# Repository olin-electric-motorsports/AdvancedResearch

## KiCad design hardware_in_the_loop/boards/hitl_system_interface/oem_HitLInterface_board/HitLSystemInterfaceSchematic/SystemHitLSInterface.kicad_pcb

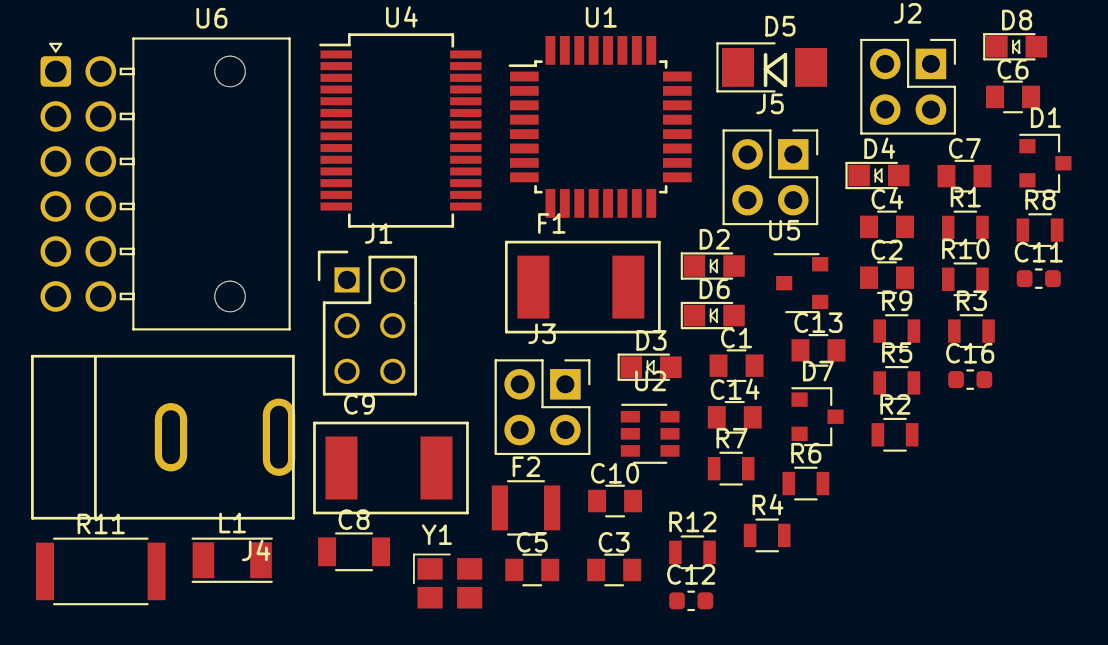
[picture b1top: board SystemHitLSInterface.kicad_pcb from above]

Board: 2 copper layers, 49 parts (0 on the bottom side), 44 nets, no tracks yet.

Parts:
C1, C3, C7, C13, C14: C_0.1uF; C_0805_OEM
C2: C_100pF; C_0805_OEM
C4, C6: C_30pF; C_0805_OEM
C5: C_2.2uF; C_0805_OEM
C8: C_22uF; C_1206_OEM
C9: C_33uF; Fuse_1812
C10: C_47uF; C_0805_OEM
C11: C_4.7uF; C_0603_1608Metric
C12, C16: C_100nF; C_0603_1608Metric
D1, D7: BAS40-00; SOT-23
D2, D3, D4, D6, D8: LED_0805; LED_0805_OEM
D5: D_Zener_18V; DO-214AA
F1: 200mA_Fuse; Fuse_1812
F2: F_500mA_16V; Fuse_1210
J1: CONN_02X03; Pin_Header_Straight_2x03
J2, J3, J5: Conn_01x04_Female; PinSocket_2x02_P2.54mm_Vertical
J4: Barrel_Jack; barrel_jack_PJ-037A
L1: L_100uH; L_100uH_OEM
R1: R_100; R_0805_OEM
R2, R3, R4, R12: R_200; R_0805_OEM
R5, R6, R7: R_10K; R_0805_OEM
R8: R_1K; R_0805_OEM
R9: R_25K; R_0805_OEM
R10: R_100K; R_0805_OEM
R11: R_0_2512; R_2512_OEM
U1: ATmega328P-AU; TQFP-32_7x7mm_P0.8mm
U2: TPS560430YF; SOT-23-6_OEM
U4: FT232RL; SSOP-28_5.3x10.2mm_P0.65mm
U5: LM3480; SOT-23-3_OEM
U6: NanoFit_RA_TH_12; NanoFit_RA_12
Y1: Crystal_SMD; Crystal_SMD_FA238

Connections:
+3V3: C14.1, J2.1, U5.1
/12V: C3.1, C5.1, D5.1, J2.3, R8.1, U2.4, U2.5
/AI1: U1.19, U6.8
/AI2: U1.22, U6.9
/AI3: U1.23, U6.10
/AI4: U1.24, U6.11
/D1: U1.25, U6.1
/D2: U1.26, U6.2
/D3: U1.32, U6.3
/D4: U1.1, U6.4
/D5: U1.11, U6.5
/D6: U1.12, U6.6
/D7: U1.13, U6.7
/MISO: J1.1, J3.4, U1.16
/MOSI: J1.4, J3.3, U1.15
/RESET: J1.5, R7.2, U1.29
/RXD: U1.30, U4.1
/SCK: J1.3, J3.2, U1.17
/SCL: J5.3, R6.2, U1.28
/SDA: J5.4, R5.2, U1.27
/SS_HitL: J3.1, U1.14
/TXD: U1.31, U4.5
/VCCUSB: C11.2, C12.2, D1.3, U4.20
GND: C1.2, C2.2, C3.2, C4.2, C5.2, C6.2, C8.2, C9.2, C10.2, C11.1, C12.1, C13.2, C14.2, C16.2, D2.1, D3.1, D4.1, D6.1, D8.1, F2.2, J1.6, J2.4, J4.1, R9.2, U1.3, U1.5, U1.21, U2.2, U4.7, U4.18, U4.21, U4.25, U4.26, U5.3, Y1.2, Y1.4
unnamed: C2.1, R1.2, U1.18
unnamed: C4.1, U1.8, Y1.1
unnamed: C6.1, U1.7, Y1.3
unnamed: C7.1, U2.1
unnamed: C7.2, L1.1, U2.6
unnamed: C8.1, C9.1, C10.1, L1.2, R10.1, R11.1
unnamed: C16.1, U4.17
unnamed: D1.1, F1.2
unnamed: D2.2, R2.1
unnamed: D3.2, R3.1
unnamed: D4.2, R4.1
unnamed: D5.2, F2.1
unnamed: D6.2, R8.2
unnamed: D7.1, R11.2, R12.1
unnamed: D8.2, R12.2
unnamed: R2.2, U1.2
unnamed: R3.2, U1.9
unnamed: R4.2, U1.10
unnamed: R9.1, R10.2, U2.3
VCC: C1.1, C13.1, D7.3, J1.2, J2.2, J4.2, R1.1, R5.1, R6.1, R7.1, U1.4, U1.6, U4.4, U5.2

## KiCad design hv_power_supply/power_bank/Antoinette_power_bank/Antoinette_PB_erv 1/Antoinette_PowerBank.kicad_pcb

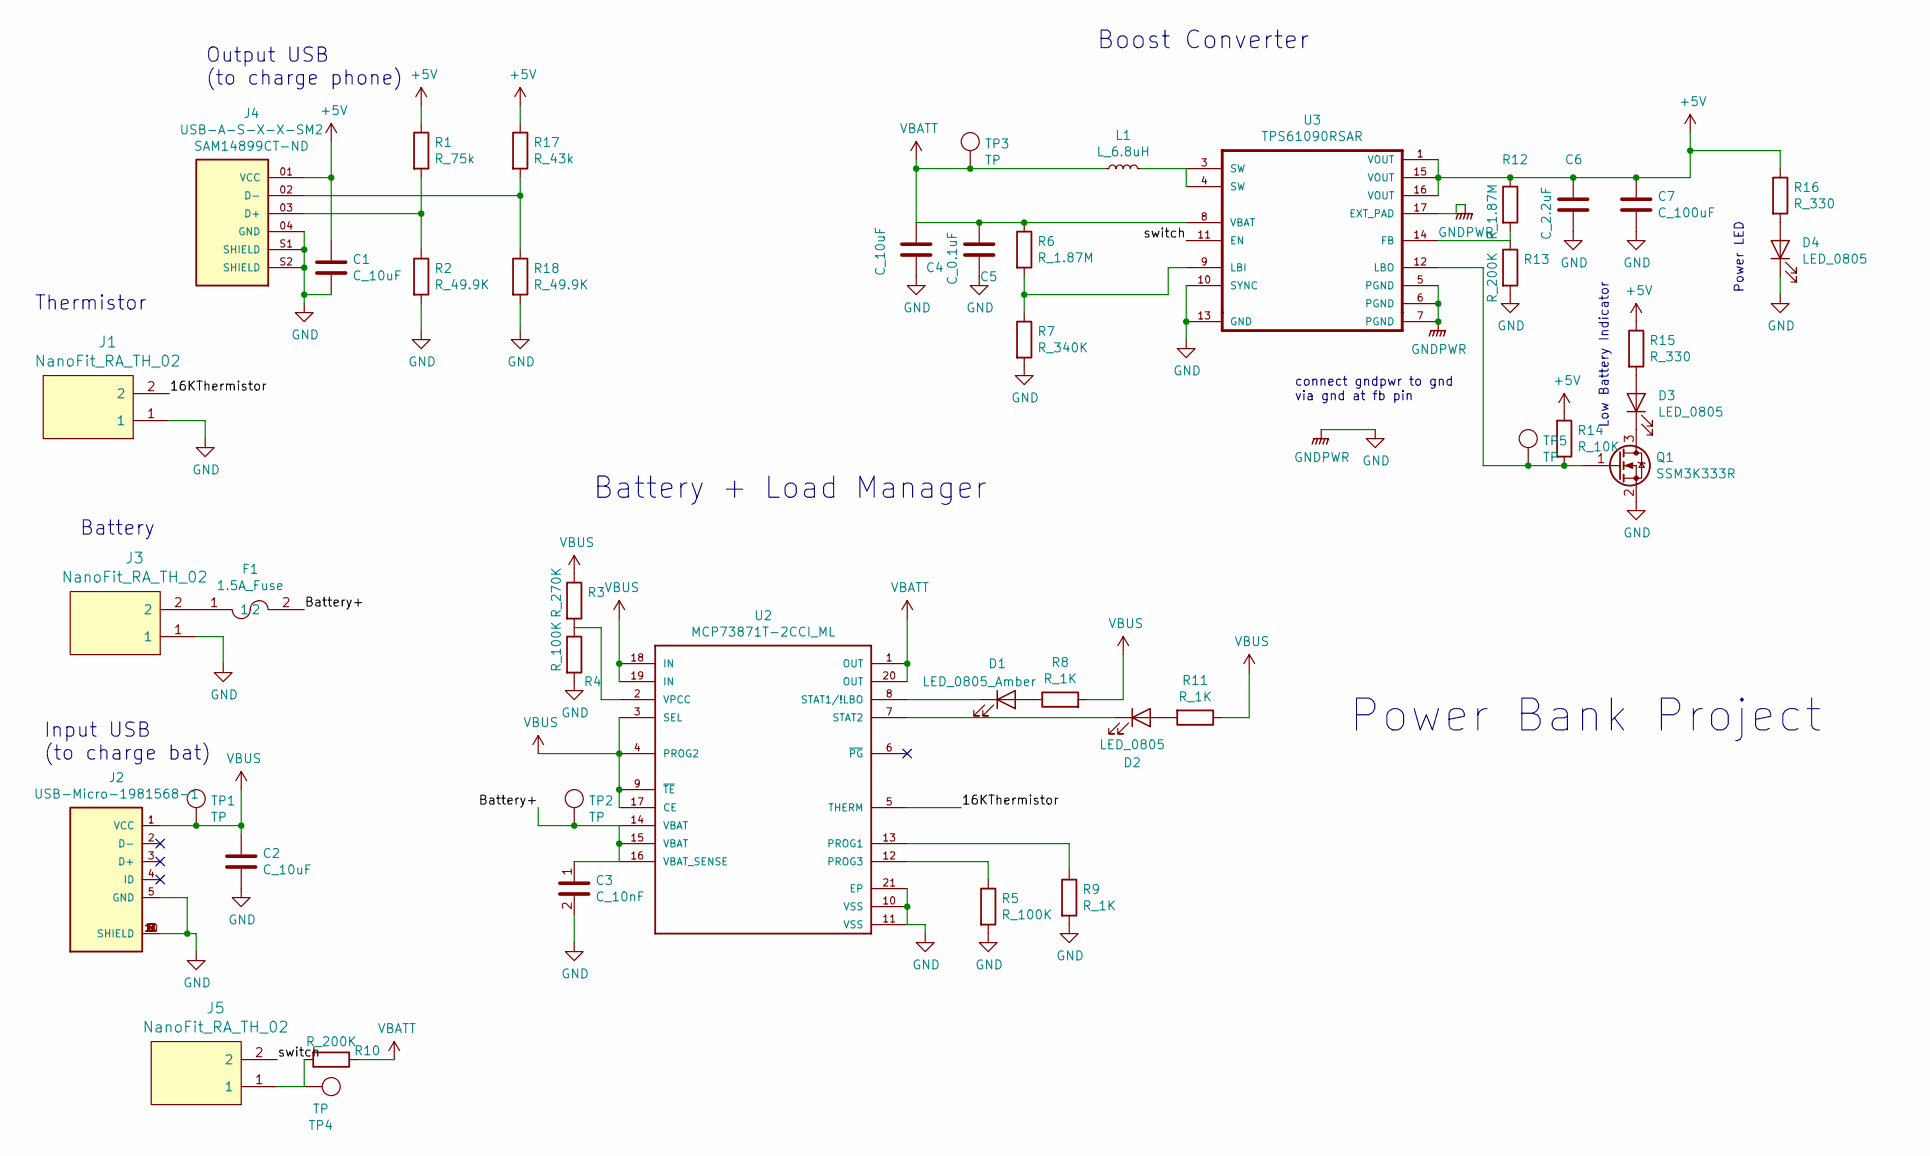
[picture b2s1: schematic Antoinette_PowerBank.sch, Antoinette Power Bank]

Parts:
C1, C2, C4: C_10uF; C_0805_OEM; MPN 1276-1052-1-ND
C3: C_10nF; C_0805_OEM; MPN 1276-1015-1-ND
C5: C_0.1uF; C_0805_OEM; MPN 478-3352-1-ND
C6: C_2.2uF; C_0805_OEM
C7: C_100uF; C_1812_4532Metric; MPN 445-1413-1-ND
D1: LED_0805_Amber; LED_0805_OEM; MPN L71517CT-ND
D2, D3, D4: LED_0805; LED_0805_OEM; MPN 475-1410-1-ND
F1: 1.5A_Fuse; Fuse_1206; MPN F1462CT-ND
J1, J3, J5: NanoFit_RA_TH_02; NanoFit_Molex_1x02x2.50mm_Angled_OEM; MPN WM14972-ND
J2: USB-Micro-1981568-1; TE_1981568-1; MPN 1981568-1
J4: USB-A-S-X-X-SM2; SAMTEC_USB-A-S-X-X-SM2; MPN SAM14899CT-ND
L1: L_6.8uH; L_100uH_OEM; MPN 445-1539-1-ND
Q1: SSM3K333R; SOT-23F; MPN SSM3K333RLFCT-ND
R1: R_75k; R_0805_OEM
R2, R18: R_49.9K; R_0805_OEM
R3: R_270K; R_0805_OEM; MPN P270KDACT-ND
R4, R5: R_100K; R_0805_OEM; MPN P100KCCT-ND
R6, R12: R_1.87M; R_0805_OEM; MPN RMCF0805FT1M82CT-ND
R7: R_340K; R_0805_OEM; MPN P300KDACT-ND
R8, R9, R11: R_1K; R_0805_OEM; MPN RNCP0805FTD1K00CT-ND
R10, R13: R_200K; R_0805_OEM; MPN P300KDACT-ND
R14: R_10K; R_0805_OEM; MPN CRS0805-FX-1002ELFCT-ND
R15, R16: R_330; R_0805_OEM; MPN RMCF0805FT330RCT-ND
R17: R_43k; R_0805_OEM
TP1, TP2, TP3, TP4, TP5: TP; tp_1.6mm; MPN 36-5006-ND
U2: MCP73871T-2CCI_ML; MCP73871T
U3: TPS61090RSAR

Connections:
+5V: C1.1, C6.1, C7.1, J4.01 (VCC), R1.1, R12.1, R14.1, R15.1, R16.1, R17.1, U3.1 (VOUT), U3.15 (VOUT), U3.16 (VOUT)
+BATT: C4.1, C5.1, L1.1, R6.1, R10.1, TP3.1, U2.1 (OUT), U2.20 (OUT), U3.8 (VBAT)
/16KThermistor: J1.2, U2.5 (THERM)
/Battery+: C3.1, F1.2, TP2.1, U2.14 (VBAT), U2.15 (VBAT), U2.16 (VBAT_SENSE)
/switch: J5.2, U3.11 (EN)
GND: C1.2, C2.2, C3.2, C4.2, C5.2, C6.2, C7.2, D4.1 (K), J1.1, J2.5 (GND), J2.6 (SHIELD), J2.7 (SHIELD), J2.8 (SHIELD), J2.9 (SHIELD), J2.10 (SHIELD), J2.11 (SHIELD), J3.1, J4.04 (GND), J4.S1 (SHIELD), J4.S2 (SHIELD), Q1.2 (S), R2.2, R4.2, R5.2, R7.2, R9.2, R13.2, R18.2, U2.10 (VSS), U2.11 (VSS), U2.21 (EP), U3.5 (PGND), U3.6 (PGND), U3.7 (PGND), U3.10 (SYNC), U3.13 (GND), U3.17 (EXT_PAD)
unnamed: D1.1 (K), U2.8 (STAT1/!LBO)
unnamed: D1.2 (A), R8.1
unnamed: D2.1 (K), U2.7 (STAT2)
unnamed: D2.2 (A), R11.2
unnamed: D3.1 (K), Q1.3 (D)
unnamed: D3.2 (A), R15.2
unnamed: D4.2 (A), R16.2
unnamed: F1.1, J3.2
unnamed: J4.02 (D-), R17.2, R18.1
unnamed: J4.03 (D+), R1.2, R2.1
unnamed: J5.1, R10.2, TP4.1
unnamed: L1.2, U3.3 (SW), U3.4 (SW)
unnamed: Q1.1 (G), R14.2, TP5.1, U3.12 (LBO)
unnamed: R3.2, R4.1, U2.2 (VPCC)
unnamed: R5.1, U2.12 (PROG3)
unnamed: R6.2, R7.1, U3.9 (LBI)
unnamed: R9.1, U2.13 (PROG1)
unnamed: R12.2, R13.1, U3.14 (FB)
VBUS: C2.1, J2.1 (VCC), R3.1, R8.2, R11.1, TP1.1, U2.3 (SEL), U2.4 (PROG2), U2.9 (~TE~), U2.17 (CE), U2.18 (IN), U2.19 (IN)

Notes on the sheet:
Output USB (to charge phone)
Thermistor
Battery
Input USB (to charge bat)
connect gndpwr to gnd via gnd at fb pin
Boost Converter
Low Battery Indicator
Power LED
Battery + Load Manager
Power Bank Project

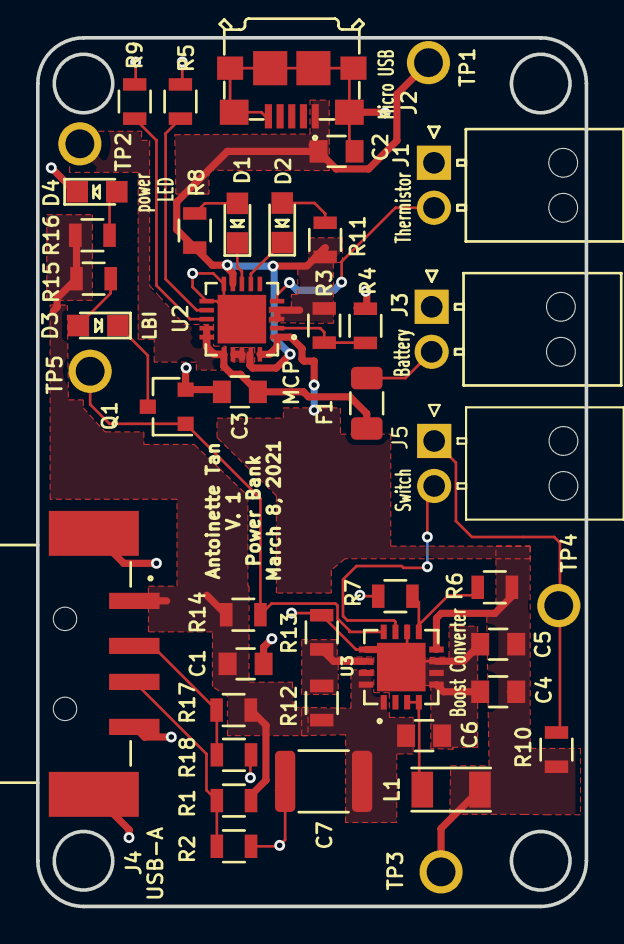
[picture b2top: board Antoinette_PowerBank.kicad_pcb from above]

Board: 2 copper layers, 30.5 x 48.3 mm, 44 parts (0 on the bottom side), 25 nets.

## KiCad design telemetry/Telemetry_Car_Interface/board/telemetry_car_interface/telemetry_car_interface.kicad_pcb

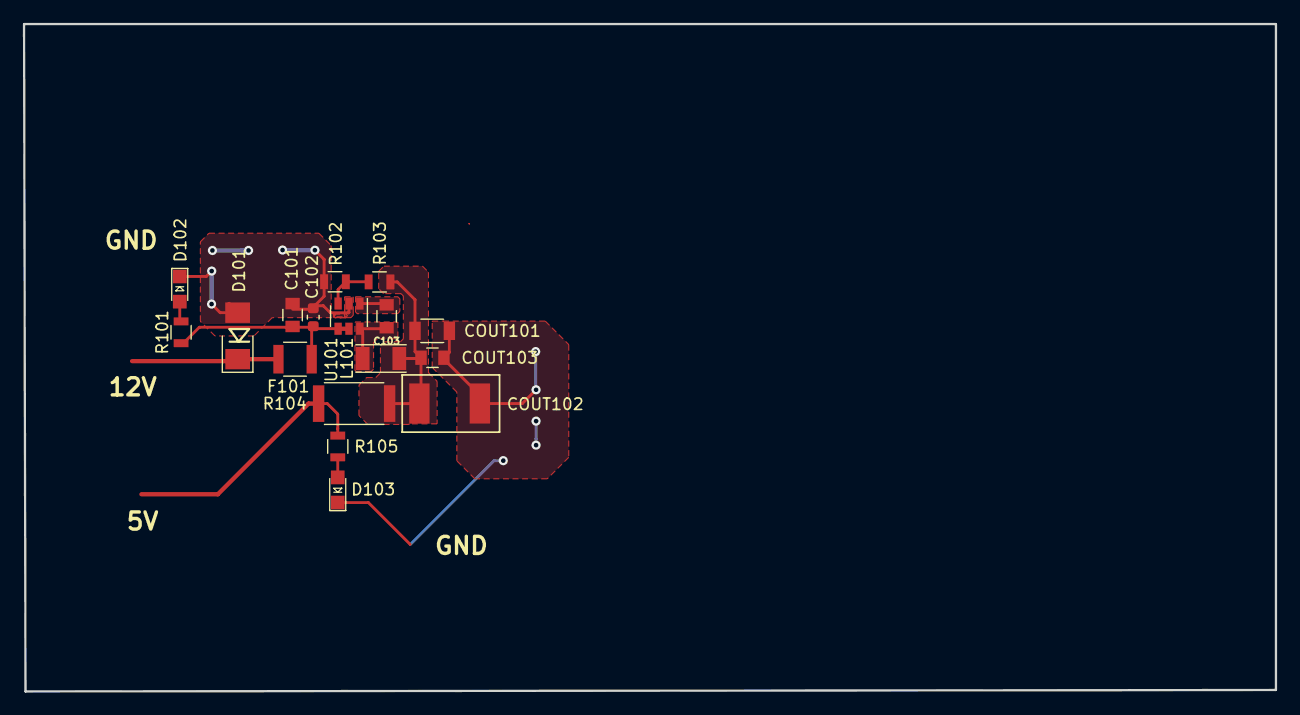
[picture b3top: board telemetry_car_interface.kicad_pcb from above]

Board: 2 copper layers, 109.3 x 58.3 mm, 17 parts (0 on the bottom side), 10 nets.

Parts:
C101, C103: C_0.1uF; C_0805_OEM
C102: C_2.2uF; C_0603_1608Metric
COUT101: C_22uF; C_1206_OEM
COUT102: C_33uF; Fuse_1812
COUT103: C_47uF; C_0805_OEM
D101: D_Zener_18V; DO-214AA
D102, D103: LED_0805; LED_0805_OEM
F101: F_500mA_16V; Fuse_1210
L101: L_100uH; L_100uH_OEM
R101: R_1K; R_0805_OEM
R102: R_25K; R_0805_OEM
R103: R_100K; R_0805_OEM
R104: R_0_2512; R_2512_OEM
R105: R_200; R_0805_OEM
U101: TPS560430YF; SOT-23-6_OEM

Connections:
/12V: D101.1, F101.2
GND: C101.2, C102.2, COUT102.2, D101.2, D102.1, D103.1, R102.2, U101.2
unnamed: C101.1, C102.1, F101.1, R101.1, U101.4, U101.5
unnamed: C103.1, U101.1
unnamed: C103.2, L101.1, U101.6
unnamed: COUT101.1, COUT102.1, COUT103.1, L101.2, R103.1, R104.1
unnamed: D102.2, R101.2
unnamed: D103.2, R105.2
unnamed: R102.1, R103.2, U101.3
VCC: R104.2, R105.1
